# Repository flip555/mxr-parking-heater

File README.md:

# MXR Parking Heater — ESPHome bridge

Turn a **MaXpeedingRods (MXR) Tuya parking heater** into a local Home Assistant
device: no phone app, no cloud, no vendor account.

There are four ways to connect, from watching only to full control: replay the
remote's 433 MHz frames, listen on the Modbus bus, replace the BLE module, or
inject frames directly into the receiver's output. All four give you state; three
give you control. Pick the one that matches how much you want to open the case.

> Built and tested against the MXR / MaXpeedingRods heater with product key
> `vmdizama`. Other Tuya heaters may speak the same protocol but will have a
> different datapoint map.

---

## The controller

Five keys — on/off, up, OK, down, settings. On/off and up/down are reachable from
this project; OK and settings are panel-only. See the
[controller page](https://github.com/flip555/mxr-parking-heater/wiki/Controller)
for display icons, connectors and the 3.3 V wiring.

---

## What you get

**Control**

- Power on / off
- **Manual** mode — pick a power level, P1–P5
- **Auto** mode — pick a target temperature and let the heater modulate
- Setpoint from 8–36 °C
- Oil prime, with a configurable backstop timer
- Every change confirmed by the heater itself, not assumed

**Monitoring**

- Live power, mode, gear and setpoint
- Current temperature and work state *(once a burner is fitted — see Status)*
- Burner telemetry block, 1 Hz *(documented, not yet mapped)*

**Behaviour that matters**

- **Survives reboots** — the last state is restored from flash and nothing is
  transmitted until boot completes, so the heater is never stomped on restart
- **Follows the panel** — press a button on the heater and Home Assistant updates
  within a second
- **Follows Home Assistant** — command it and the heater applies it and confirms
- **Fully local** — Tuya frames and Modbus on the wire, ESPHome on your LAN. No
  internet, no account, no app

---

## Three ways to connect

| | **Tier 0 — RF** | **Tier 1 — Monitor** | **Tier 2 — Control** |
|---|---|---|---|
| Soldering | none | none | remove the BT3L |
| Wires | 3 + RF module | 3 | 4 |
| Control from HA | yes, coarse | no | yes, precise |
| Mode switching | no | no | **yes** |
| State + telemetry | yes | yes | yes |
| Hardware | ESP32 + FS1000A | D1 mini is enough | ESP32 |

- **Tier 0** — replay the remote's own 433 MHz frames. No soldering, but the
  remote only offers on/off and up/down, so control is coarse and mode is
  panel-only.
- **Tier 1** — listen on the Modbus mirror. Read-only, one data wire.
- **Tier 2** — remove the BT3L and drive the Tuya UART. Full control including
  mode changes and gear.
Start with Tier 1 to prove the wiring, then move to Tier 0 or Tier 2 depending on
whether you want control without opening the case.

---

## Quick start

1. **Pick a tier** — the table above.
2. **Wire it** — see [Wiring](https://github.com/flip555/mxr-parking-heater/wiki/Wiring).
3. **Flash it** — one of:

   | Tier | Config |
   |---|---|
   | 0 — RF | `esphome/tier0-rf-modbus.yaml` |
   | 1 — Monitor | `esphome/tier1-monitor.yaml` |
   | 2 — Control | `esphome/tier2-control.yaml` |

4. **Add it** — the device appears in Home Assistant via ESPHome.

Full instructions, photos and pitfalls: **[the wiki](https://github.com/flip555/mxr-parking-heater/wiki)**.

| Page | |
|---|---|
| [Wiring](https://github.com/flip555/mxr-parking-heater/wiki/Wiring) | pin by pin, all four tiers |
| [Controller](https://github.com/flip555/mxr-parking-heater/wiki/Controller) | keys, icons, connectors |
| [Tier 0 — RF](https://github.com/flip555/mxr-parking-heater/wiki/Tier-0-RF) | 433 MHz replay, keyfob IDs |
| [Tier 1 — Monitor](https://github.com/flip555/mxr-parking-heater/wiki/Tier-1-Monitor) | three wires, no soldering |
| [Tier 2 — Control](https://github.com/flip555/mxr-parking-heater/wiki/Tier-2-Control) | module removal and full control |
| [Troubleshooting](https://github.com/flip555/mxr-parking-heater/wiki/Troubleshooting) | silent bus, resets, brownouts |
| [FAQ](https://github.com/flip555/mxr-parking-heater/wiki/FAQ) | scope, safety, why it works this way |

---

## Requirements

- MaXpeedingRods / MXR Tuya parking heater (product key `vmdizama`)
- ESP32 (Tier 0, 2, 3) or ESP8266 / D1 mini (Tier 1 monitor)
- FS1000A 433 MHz transmitter (Tier 0)
- ESPHome 2025.x or newer
- Home Assistant, if you want the entities — the firmware runs standalone too

---

## Status

**Working:** power, mode, gear, setpoint, state persistence, state correction from
both the panel and Home Assistant, oil prime, and a Modbus decoder for every
controller state change.

**Not yet:** the burner telemetry block. The controller polls 14 registers at
`0x4000` once a second, but nothing answers until a burner is attached — so those
registers are documented as *unknown* rather than guessed.

**Also missing:** current temperature and work state datapoints. They exist and
are mapped from a third-party source, but have not been observed on hardware here.

---

## How it works, briefly

The heater's controller is a Tuya MCU device. Its BT3L module is only a
BLE-to-UART bridge, so an ESP can take its place on the same UART. Separately, the
controller talks Modbus RTU to the burner over a single wire, and mirrors every
settings change onto that bus.

For **Tier 0/3** there is no Tuya at all: the ESP builds the controller's 433 MHz
remote frame itself (20-bit ID + 4-bit button) and either transmits it or injects
it into the receiver's output. State still comes from Modbus.

So: **Tuya for commands, Modbus for state** — or **RF for commands** when you
don't want to open the case. The ESP keeps its own copy of the
state and treats both buses as corrections, because this firmware has no working
"read everything" command.

Technical detail — frame formats, datapoint ids, register bitfields, and the
documented read-all bug — lives in [`docs/`](docs/) and on the wiki. This README
stays about what the thing *does*.

---

## Repository layout

```
esphome/     ready-to-flash configs (monitor + control)
docs/        protocol reference: Tuya, Modbus, hardware teardown
wiki         setup guides, troubleshooting, FAQ
```

---

## Contributing

The most useful thing you can send is a **capture**: raw frames plus what the
panel was showing at that moment. That is how the register map gets finished.

---

## Licence

MIT.

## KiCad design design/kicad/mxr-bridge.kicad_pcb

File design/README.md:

# ESP32-C3 heater bridge — board design

A complete 2-layer design for the MXR heater bridge. Everything here is what you
enter into KiCad or EasyEDA; the netlist, BOM and layout rules are the design.

---

## 1. Specification

| Item | Value |
|---|---|
| Board size | 70 × 45 mm |
| Layers | 2 (top signal, bottom ground pour) |
| Thickness | 1.6 mm |
| Copper | 1 oz (35 µm) |
| Min track | 0.2 mm, signals 0.25 mm |
| Min clearance | 0.2 mm (0.3 mm on 3.3 V) |
| Vias | 0.3 mm drill / 0.6 mm pad |
| Surface finish | HASL lead-free |
| Module | ESP32-C3-WROOM-02 (or `-02U` for external antenna) |

### Track widths

| Net class | Width | Why |
|---|---|---|
| 3V3 input from J1 | **0.8 mm** | 350 mA peaks with margin |
| 3V3 distribution | **0.5 mm** | ~1 A at 10 °C rise, 1 oz |
| GND | **pour + 0.5 mm** | plane on bottom layer |
| Signals (UART, I²C, 1-Wire) | **0.25 mm** | |
| USB D+ / D− | **0.2 mm, 90 Ω diff** | ~0.15 mm gap, 1.6 mm FR4 |
| Modbus | **0.3 mm** | single-ended, keep short |

---

## 2. Power tree

```
J1 (controller 3.3V) ──F1 0.5A──► D2 SS14 ──┐
                                            ├──► +3V3 rail
USB-C VBUS ──► U2 AP2112K-3.3 ──────────────┘
```

- **D2** stops the LDO back-feeding the controller rail when USB is plugged in.
- The LDO wins when USB is present (3.3 V vs 3.0 V after the Schottky).
- C1 470 µF sits at the module's 3V3 pad — the C3 pulls ~350 mA peaks on Wi-Fi TX.

---

## 3. Pin assignment

| GPIO | Net | Connector |
|---|---|---|
| IO0 | I2C_SDA | J6 pin 3 |
| IO1 | I2C_SCL | J6 pin 4 |
| IO2 | RF_RX | J5 pin 3 |
| IO3 | NTC_ADC | J8 pin 2 |
| IO4 | TUYA_TX | J2 pin 2 |
| IO5 | TUYA_RX | J2 pin 3 |
| IO6 | MODBUS_RX | J3 pin 2 |
| IO7 | RF_TX | J4 pin 3 |
| IO8 | LED (active low) | LED1 cathode |
| IO9 | BOOT button | SW2 |
| IO10 | ONEWIRE | J7 pin 3 |
| IO18 | USB_D− | J10 |
| IO19 | USB_D+ | J10 |
| IO20 | UART0_RX | J9 pin 4 |
| IO21 | UART0_TX | J9 pin 3 |
| EN | RESET | SW1, R1, C4 |

Strapping pins: **IO2, IO8, IO9**. IO2 is driven by the RF receiver (idles high),
IO8 is pulled high by its internal pull-up and only sinks LED current when driven
low, IO9 has the BOOT button to GND. All safe at reset.

---

## 4. Schematics by block

### Module

- 3V3 → pin 3, GND → pins 1, 2, 11 and the 3×3 thermal grid + pin 49
- EN → R1 10 kΩ to 3V3, C4 100 nF to GND, SW1 to GND
- C2 10 µF + C3 100 nF at 3V3, C1 470 µF nearby

### Connectors

| Ref | Pins | Function |
|---|---|---|
| J1 | 2 | 3.3 V in from controller (F1, D1 TVS on this) |
| J2 | 3 | GND, TUYA_TX (→ module pad 16), TUYA_RX (← pad 15) |
| J3 | 3 | GND, MODBUS_RX, 3V3 (optional feed) |
| J4 | 3 | 3V3, GND, RF_TX |
| J5 | 3 | 3V3, GND, RF_RX |
| J6 | 4 | 3V3, GND, I2C_SDA, I2C_SCL |
| J7 | 3 | 3V3, GND, ONEWIRE |
| J8 | 3 | 3V3, NTC_ADC, GND |
| J9 | 4 | 3V3, GND, UART0_TX, UART0_RX |
| J10 | USB-C | VBUS, GND, D+, D−, CC1, CC2 |

### Passives

- R3, R4: 4.7 kΩ I²C pull-ups to 3V3
- R5: 4.7 kΩ 1-Wire pull-up to 3V3
- R6: 10 kΩ NTC divider, 3V3 → NTC_ADC (probe to GND)
- R7: 1 kΩ LED series to 3V3, cathode to IO8
- R8, R9: 5.1 kΩ CC1/CC2 to GND (USB-C device)
- U3: USBLC6-2SC6 ESD array on D+/D−

---

## 5. Placement

Board outline 60 × 40 mm, USB-C on the short edge.

```
┌──────────────────────────────────────────────┐
│  [J10 USB-C]   U2 LDO   C1 470µF             │
│                                              │
│   ┌─────────────────┐        J1 3V3 (edge)   │
│   │  C3-MINI-1      │                        │
│   │  (antenna edge  │        J3 MODBUS       │
│   │   overhangs)    │                        │
│   └─────────────────┘        J2 TUYA         │
│                                              │
│   SW1  SW2   LED1            J4 RF TX        │
│                              J5 RF RX        │
│   J6 I2C   J7 1-Wire   J8 NTC   J9 UART0     │
└──────────────────────────────────────────────┘
   ▲ keepout: no copper under antenna
```

Rules:

1. **Module antenna overhangs the board edge**; no copper on any layer under the
   keepout rectangle, including the ground pour.
2. **C1, C2, C3 within 5 mm of the module 3V3 pad**, on the same side.
3. **USB D+/D− as a pair**, no stubs, length-matched within 2 mm, reference plane
   continuous underneath (no pour splits).
4. **Tuya UART traces short** (< 30 mm) and away from the LDO switching node.
5. **Modbus** routed on the top layer with ground pour either side; it is
   single-ended and picks up noise easily.
6. **Headers on the edges**, silkscreen-labelled, pin 1 marked.
7. **Thermal grid**: 9 vias under the module GND grid to the bottom pour.

---

## 6. Fabrication

Standard 2-layer, no special requirements. Order 5 boards; the BOM is under £8 in
single quantities.

## Generated KiCad project

`design/kicad/` contains a generated, validated project:

| File | State |
|---|---|
| `mxr-bridge.kicad_sch` | **validated** — kicad-cli exports a netlist with all nets |
| `mxr-bridge.kicad_pcb` | outline, 31 footprints placed, nets assigned, GND zone |
| `mxr-bridge.zip` | the above, zipped for EasyEDA Pro import |

**Not finished:** routing and courtyard tidy-up. The board is placed, not routed —
DRC reports unconnected items and some courtyard overlaps. Open it in KiCad and
route, or say the word and I'll continue.

Note: the module changed to **WROOM-02** because that is what KiCad ships a symbol
and footprint for; the MINI-1 needs a custom footprint. The pin map is unchanged.

---

**Assembly order** (hand-solder friendly):

1. Module (stencil or drag-solder the castellations)
2. LDO, TVS, polyfuse, Schottky
3. Passives 0603, then USB-C
4. Headers last

The antenna keepout makes the module the only part that must be perfectly placed —
everything else tolerates a millimetre of slop.

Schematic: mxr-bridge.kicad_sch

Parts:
C1: 470uF; CP_Elec_6.3x5.4
C2: 10uF; C_0805_2012Metric
C3, C4: 100nF; C_0603_1608Metric
D1: SMAJ3.3A; D_SMA
D2: SS14; D_SMA
F1: MF-R050; Fuse_Bourns_MF-RG500
J1: 3V3 IN; JST_XH_B2B-XH-A_1x02_P2.50mm_Vertical
J2: TUYA; JST_XH_B3B-XH-A_1x03_P2.50mm_Vertical
J3: MODBUS; JST_XH_B3B-XH-A_1x03_P2.50mm_Vertical
J4: RF TX; JST_XH_B3B-XH-A_1x03_P2.50mm_Vertical
J5: RF RX; JST_XH_B3B-XH-A_1x03_P2.50mm_Vertical
J6: I2C; JST_XH_B4B-XH-A_1x04_P2.50mm_Vertical
J7: 1-WIRE; JST_XH_B3B-XH-A_1x03_P2.50mm_Vertical
J8: NTC; JST_XH_B3B-XH-A_1x03_P2.50mm_Vertical
J9: UART0; JST_XH_B4B-XH-A_1x04_P2.50mm_Vertical
J10: USB-C; USB_C_Receptacle_GCT_USB4085
LED1: LED; LED_0805_2012Metric
R1, R6: 10k; R_0603_1608Metric
R3, R4, R5: 4.7k; R_0603_1608Metric
R7: 1k; R_0603_1608Metric
R8, R9: 5.1k; R_0603_1608Metric
SW1: RESET; SW_PUSH_6mm
SW2: BOOT; SW_PUSH_6mm
U1: ESP32-C3-WROOM-02
U2: AP2112K-3.3; SOT-23-5
U3: USBLC6-2SC6; SOT-23-6

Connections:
+3V3: C1.1, C2.1, C3.1, D2.2 (A), J3.3, J4.1, J5.1, J6.1, J7.1, J8.1, J9.1, R1.1, R3.1, R4.1, R5.1, R6.1, R7.1, U1.1 (3V3), U2.5
+3V3_RAW: D1.1 (A1), D2.1 (K), F1.2
BOOT_BTN: SW2.1, U1.8 (IO9)
EN: C4.1, R1.2, SW1.1, U1.2 (EN)
GND: C1.2, C2.2, C3.2, C4.2, D1.2 (A2), J1.2, J2.1, J3.1, J4.2, J5.2, J6.2, J7.2, J8.3, J9.2, J10.A1 (GND), J10.A12 (GND), J10.B1 (GND), J10.B12 (GND), R8.2, R9.2, SW1.2, SW2.2, U1.9 (GND), U1.19 (GND), U2.2, U3.2
I2C_SCL: J6.4, R4.2, U1.17 (IO1)
I2C_SDA: J6.3, R3.2, U1.18 (IO0)
LED_A: LED1.1 (K), R7.2
LED_K: LED1.2 (A), U1.7 (IO8)
MODBUS_RX: J3.2, U1.5 (IO6)
NTC_ADC: J8.2, R6.2, U1.15 (IO3)
ONEWIRE: J7.3, R5.2, U1.10 (IO10)
PWR_IN: F1.1, J1.1
RF_RX: J5.3, U1.16 (IO2)
RF_TX: J4.3, U1.6 (IO7)
TUYA_RX: J2.3, U1.4 (IO5)
TUYA_TX: J2.2, U1.3 (IO4)
UART0_RX: J9.4, U1.11 (IO20/RXD)
UART0_TX: J9.3, U1.12 (IO21/TXD)
USB_CC1: J10.A5 (CC1), R8.1
USB_CC2: J10.B5 (CC2), R9.1
USB_DN: J10.A7 (D-), J10.B7 (D-), U1.13 (IO18), U3.1, U3.6
USB_DP: J10.A6 (D+), J10.B6 (D+), U1.14 (IO19), U3.3, U3.4
VIN_USB: J10.A4 (VBUS), J10.A9 (VBUS), J10.B4 (VBUS), J10.B9 (VBUS), U2.1, U2.3, U3.5

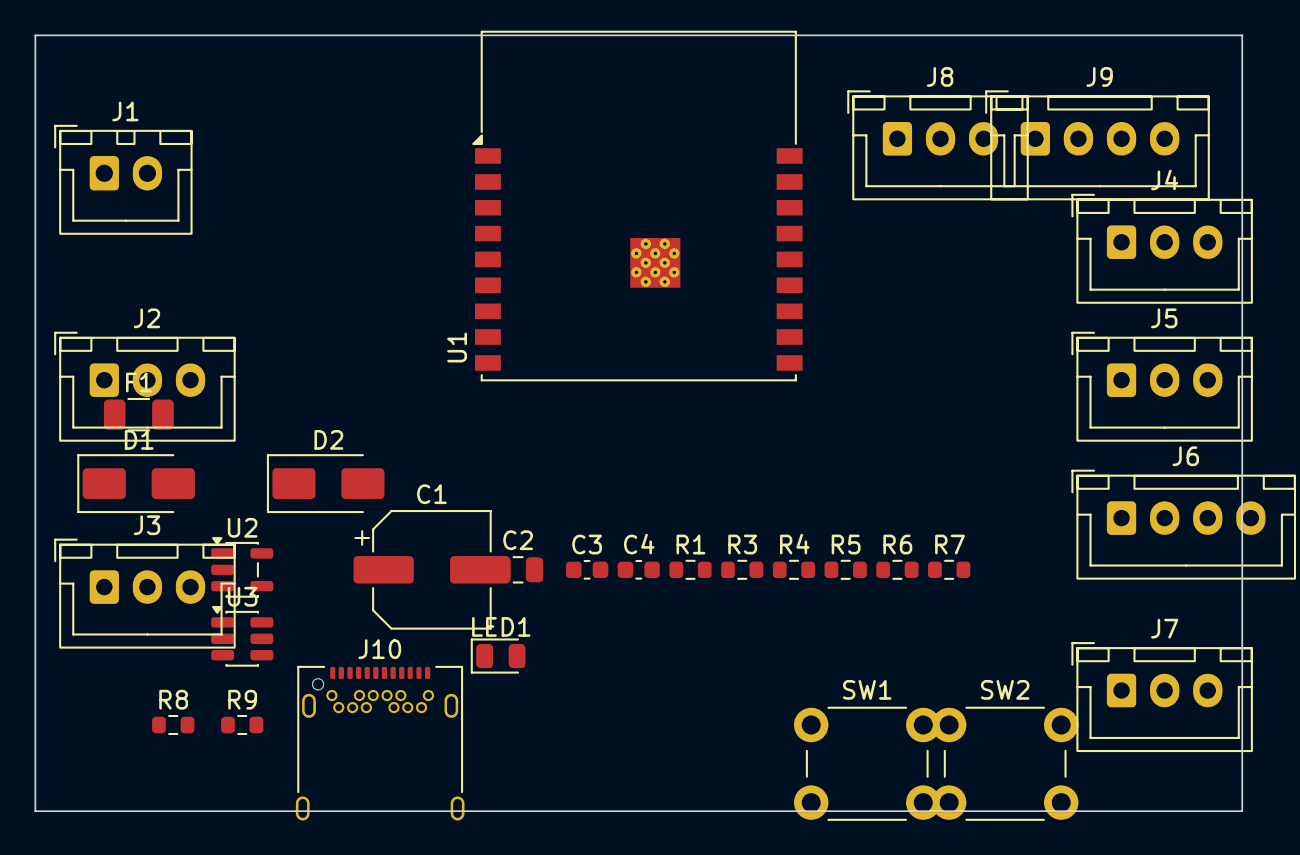
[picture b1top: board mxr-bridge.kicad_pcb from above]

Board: 2 copper layers, 70.0 x 45.0 mm, 31 parts (0 on the bottom side), 24 nets, no tracks yet.

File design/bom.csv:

qty,ref,value,package,notes
1,U1,ESP32-C3-WROOM-02,module 18x20 mm,"-02U variant for external antenna"
1,U2,AP2112K-3.3,SOT-23-5,"600 mA LDO, USB power path"
1,U3,USBLC6-2SC6,SOT-23-6,"ESD on USB D+/D-"
1,D1,SMAJ3.3A,SMA,"TVS on 3.3 V input"
1,D2,SS14,SMA,"blocks LDO back-feed to controller rail"
1,F1,0.5A fuse,1206,"polyfuse or slow-blow"
1,C1,470uF 6.3V,electrolytic 6.3x5.4,"bulk at module 3V3"
1,C2,10uF 10V,0805,"decoupling"
4,C3-C6,100nF 16V,0603,"module + LDO decoupling"
1,R1,10k,0603,"EN pull-up"
1,R3,4.7k,0603,"I2C SDA pull-up"
1,R4,4.7k,0603,"I2C SCL pull-up"
1,R5,4.7k,0603,"1-Wire pull-up"
1,R6,10k,0603,"NTC divider (1%)"
1,R7,1k,0603,"LED series"
2,R8-R9,5.1k,0603,"USB-C CC resistors"
1,LED1,LED green,0805,"active low on IO8"
2,SW1-SW2,tact switch 6x6,THT,"RESET and BOOT"
1,J1,JST-XH 2-pin,THT,"3.3 V in from controller"
1,J2,JST-XH 3-pin,THT,"Tuya UART"
1,J3,JST-XH 3-pin,THT,"Modbus"
1,J4,JST-XH 3-pin,THT,"RF transmitter"
1,J5,JST-XH 3-pin,THT,"RF receiver"
1,J6,JST-XH 4-pin,THT,"I2C sensors"
1,J7,JST-XH 3-pin,THT,"DS18B20"
1,J8,JST-XH 3-pin,THT,"NTC probe"
1,J9,JST-XH 4-pin,THT,"UART0 console"
1,J10,USB_C_Receptacle_Amphenol_12401548E4-2A,SMD,"USB 2.0 device"
